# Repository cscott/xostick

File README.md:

This is a simple Open Hardware peripheral for the OLPC XO-1/1.5/1.75/4.

The files are created using Eagle 6.2.0 on Linux and the SparkFun
footprint libraries.

Some details about the design:

1. Supporting using either the ATtiny85 (lowest cost) or the ATtiny861
   (14 I/Os, slightly more expensive).
2. Based on the Sparkfun AVR Stick
    http://www.sparkfun.com/products/9147
   and thus software will be based on
    http://www.obdev.at/vusb/
   Note that the USB port has been moved to PB3/4 so software for the
   SparkFun AVR Stick will not work without modification.
3. The PCB we're working with is 0.8mm (0.031"); a USB plug "is supposed to be
   2.4mm (0.093") but you can get away with 1.6mm (0.062")" (thanks, djgpp)
   Our solution is to put two breakaway tabs on the back of the board.  You
   can break them off and glue them below the USB fingers to make it stay in
   the port better/at all.  One gotcha is that break away PCBs tend to stress
   nearby traces; I've tried to give them adequate clearance.  We're also
   putting copper fills on the PCBs to make them thicker (thanks again, djgpp).
   The PCB we have also has 4 layers, but I've routed this board with only
   the top and bottom so that 2 layer reproductions will work just fine as
   well.  The inner two layers are ground and power planes, which don't
   need to be present to connect the ground and power nets.
4. I'm attempting to bring BOM below $1/student and part count down as low as
   possible as well.  As a result, we're skimping a bit on ferrites and
   bypass caps.
5. There are pads for populating a mini USB B connector, so you can
   put this on a cable (and avoid the glue-the-PCBs-together dance).
6. The XO Stick has a standard arduino shield pinout.  This lets it be
   piggybacked on another XO Stick for programming, or piggy backed on
   an XOrduino to control a turtle robot.  Standard arduino shields will
   probably *not* work, since not all pins are connected -- but they might!
7. To program one XO Stick from an XOrduino, the RST header on the
   target should be put in the "PROG" position so that the programmer
   can drive it via arduino pin 0.  To program an XO Stick from another
   XO Stick, both RST headers should be in the "NORM" position, and
   the programmer needs to have the RSTDISBL fuse programmed, so that it
   can use PB5 ('85) or PB7 ('861) as an output.  Note that once RSTDISBL
   is programmed, the device can't be programmed using the ICSP port
   until RSTDISBL is unprogrammed using the high-voltage programming method.
8. The XO Stick currently needs an external programmer.
   Can we write a USB DFU bootloader using v-usb?
   Something like:

        http://www.obdev.at/products/vusb/usbasploader.html
        http://embedded-creations.com/projects/attiny85-usb-bootloader-overview/
        https://github.com/embedded-creations/USBaspLoader-tiny85

  -- C. Scott Ananian, 2012-06-09; revised 2012-07-30, 2012-08-08

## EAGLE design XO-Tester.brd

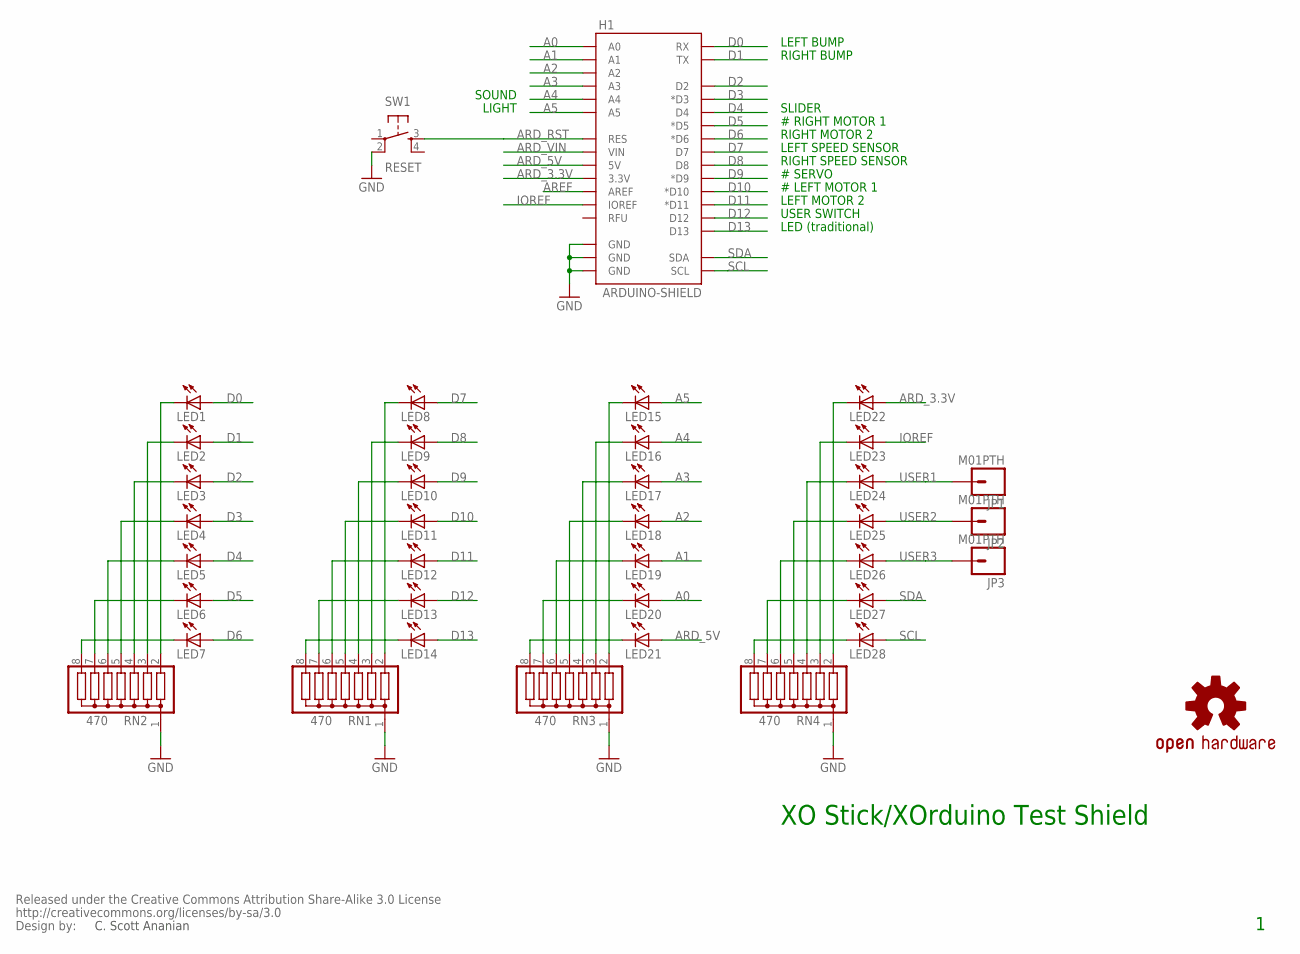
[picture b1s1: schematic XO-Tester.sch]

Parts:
H1: ARDUINO-SHIELD; ARDUINO-SHIELD-VIAS-HOLES
JP1, JP2, JP3: M01PTH; 1X01
LED1, LED2, LED3, LED4, LED5, LED6, LED7, LED8, LED9, LED10, LED11, LED12, LED13, LED14, LED15, LED16, LED17, LED18, LED19, LED20, LED21, LED22, LED23, LED24, LED25, LED26, LED27, LED28: LED3MM-KIT
RN1, RN2, RN3, RN4: 470; SIL8
SW1: RESET; TACTILE-PTH
U$1: OSHW-LOGOM; OSHW-LOGO-M
U$4: CREATIVE_COMMONS

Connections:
A0: H1.A0, LED20.A
A1: H1.A1, LED19.A
A2: H1.A2, LED18.A
A3: H1.A3, LED17.A
A4: H1.A4, LED16.A
A5: H1.A5, LED15.A
ARD_3.3V: H1.3.3V, LED22.A
ARD_5V: H1.5V, LED21.A
ARD_RST: H1.RES, SW1.3
ARD_VIN: H1.VIN
AREF: H1.AREF
D0: H1.RX, LED1.A
D1: H1.TX, LED2.A
D2: H1.D2, LED3.A
D3: H1.D3 (*D3), LED4.A
D4: H1.D4, LED5.A
D5: H1.D5 (*D5), LED6.A
D6: H1.D6 (*D6), LED7.A
D7: H1.D7, LED8.A
D8: H1.D8, LED9.A
D9: H1.D9 (*D9), LED10.A
D10: H1.D10 (*D10), LED11.A
D11: H1.D11 (*D11), LED12.A
D12: H1.D12, LED13.A
D13: H1.D13, LED14.A
GND: H1.GND@0 (GND), H1.GND@1 (GND), H1.GND@2 (GND), RN1.1, RN2.1, RN3.1, RN4.1, SW1.2
IOREF: H1.IOREF, LED23.A
unnamed: LED8.K (C), RN1.2
unnamed: LED9.K (C), RN1.3
unnamed: LED1.K (C), RN2.2
unnamed: LED2.K (C), RN2.3
unnamed: LED3.K (C), RN2.4
unnamed: LED4.K (C), RN2.5
unnamed: LED5.K (C), RN2.6
unnamed: LED6.K (C), RN2.7
unnamed: LED7.K (C), RN2.8
unnamed: LED10.K (C), RN1.4
unnamed: LED11.K (C), RN1.5
unnamed: LED12.K (C), RN1.6
unnamed: LED13.K (C), RN1.7
unnamed: LED14.K (C), RN1.8
unnamed: LED15.K (C), RN3.2
unnamed: LED16.K (C), RN3.3
unnamed: LED17.K (C), RN3.4
unnamed: LED18.K (C), RN3.5
unnamed: LED19.K (C), RN3.6
unnamed: LED20.K (C), RN3.7
unnamed: LED21.K (C), RN3.8
unnamed: LED22.K (C), RN4.2
unnamed: LED23.K (C), RN4.3
unnamed: LED24.K (C), RN4.4
unnamed: LED25.K (C), RN4.5
unnamed: LED26.K (C), RN4.6
unnamed: LED27.K (C), RN4.7
unnamed: LED28.K (C), RN4.8
SCL: H1.SCL, LED28.A
SDA: H1.SDA, LED27.A
USER1: JP1.1, LED24.A
USER2: JP2.1, LED25.A
USER3: JP3.1, LED26.A

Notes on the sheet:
C. Scott Ananian
XO Stick/XOrduino Test Shield
# RIGHT MOTOR 1
# SERVO
# LEFT MOTOR 1
LEFT BUMP
RIGHT BUMP
SLIDER
RIGHT MOTOR 2
LEFT SPEED SENSOR
RIGHT SPEED SENSOR
LEFT MOTOR 2
USER SWITCH
LED (traditional)
SOUND
LIGHT

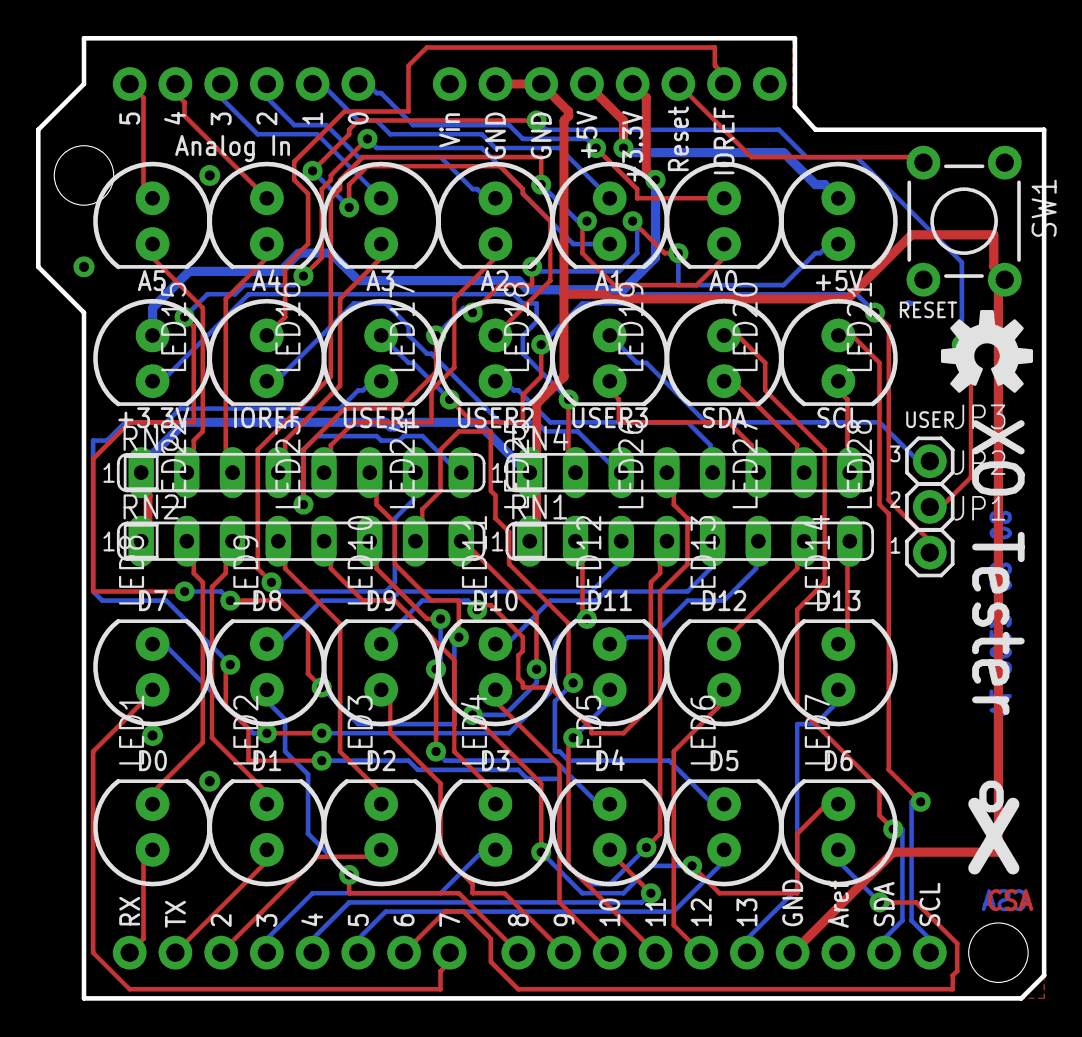
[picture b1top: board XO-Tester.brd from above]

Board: 2 copper layers, 55.9 x 53.3 mm, 39 parts (0 on the bottom side), 58 nets.

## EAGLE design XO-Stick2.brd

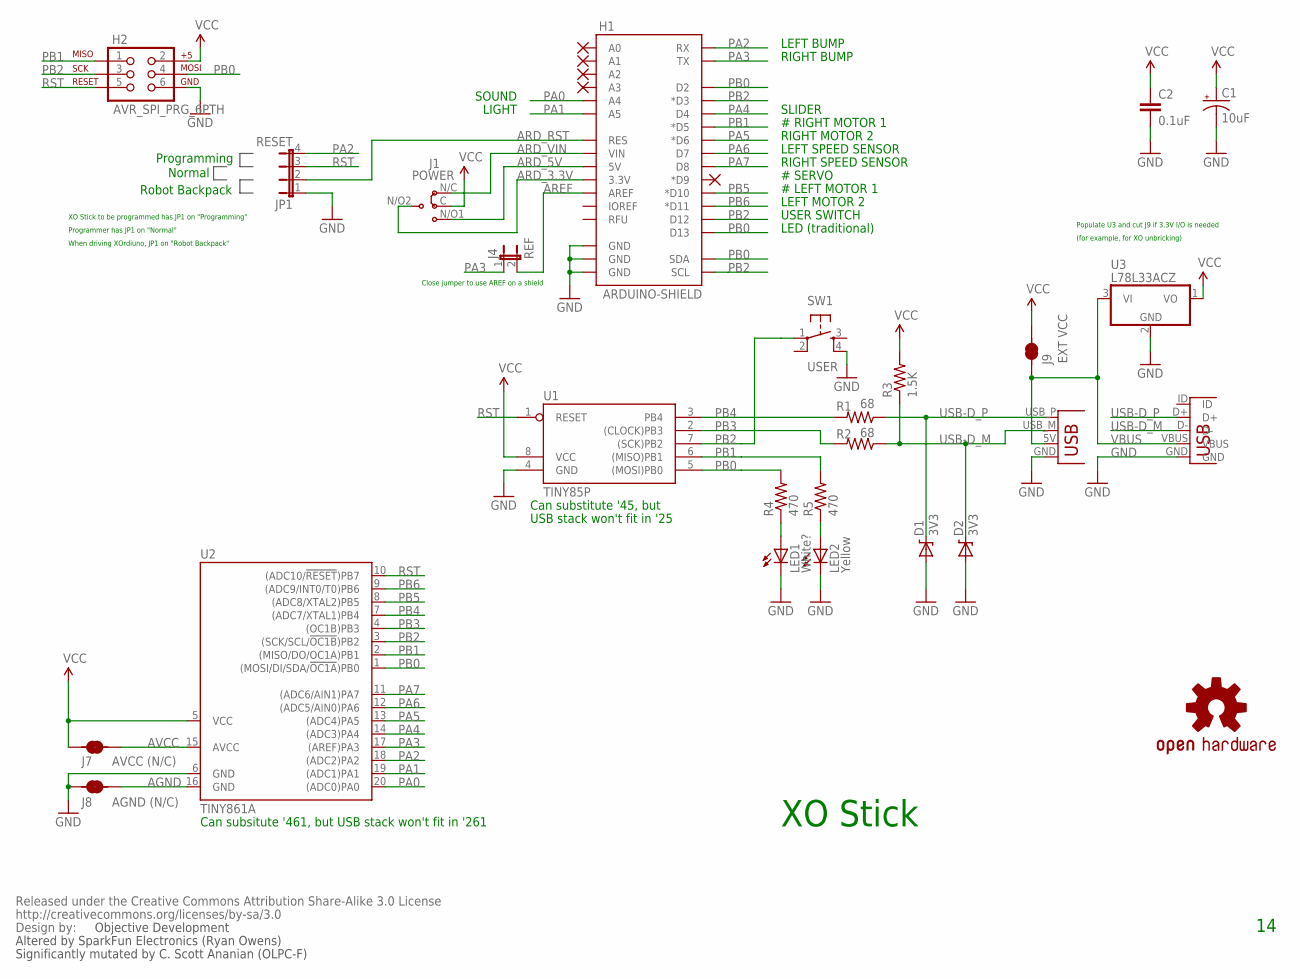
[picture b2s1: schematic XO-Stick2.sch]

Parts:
C1: 10uF; CPOL-RADIAL-10UF-25V
C2: 0.1uF; CAP-PTH-SMALL-KIT
D1, D2: 3V3; DIODE-ZENER
H1: ARDUINO-SHIELD; ARDUINO-SHIELD-VIAS-HOLES
H2: AVR_SPI_PRG_6PTH; 2X3
J1: POWER; JP4-TRACE-NOCONFLICT
J4: REF; SJ-2S-NO
J7: AVCC (N/C); SJ-2S-BOT-TRACE-NOCONFLICT
J8: AGND (N/C); SJ-2S-BOT-TRACE-NOCONFLICT
J9: EXT VCC; SJ-2S-BOT-TRACE-NOCONFLICT-PAD
JP1: RESET; JP4
LED1: White?; LED3MM-KIT
LED2: Yellow; LED3MM-KIT
R1, R2: 68; AXIAL-0.3-KIT
R3: 1.5K; AXIAL-0.3-KIT
R4, R5: 470; AXIAL-0.3-KIT
SW1: USER; TACTILE-PTH
U1: TINY85P; DIL08
U2: TINY861A; DIL20
U3: L78L33ACZ; TO92
U$1: OSHW-LOGOM; OSHW-LOGO-M
U$4: CREATIVE_COMMONS
X1: USBPCB; USB-A-PCB
X2: USBMINIB; USB-MB-H2

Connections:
AGND: J8.2, U2.16 (GND)
ARD_3.3V: H1.3.3V, J1.N/O2
ARD_5V: H1.5V, J1.N/O1
ARD_RST: H1.RES, JP1.2
ARD_VIN: H1.VIN, J1.N/C
AREF: H1.AREF, J4.2
AVCC: J7.2, U2.15 (AVCC)
GND: C1.2 (-), C2.2, D1.P$2 (A), D2.P$2 (A), H1.GND@0 (GND), H1.GND@1 (GND), H1.GND@2 (GND), H2.6, J8.1, JP1.1, LED1.K (C), LED2.K (C), SW1.4, U1.4 (GND), U2.6 (GND), U3.2 (GND), X1.GND, X2.GND
unnamed: LED1.A, R4.P$1 (1)
unnamed: LED2.A, R5.P$1 (1)
PA0: H1.A4, U2.20 ((ADC0)PA0)
PA1: H1.A5, U2.19 ((ADC1)PA1)
PA2: H1.RX, JP1.4, U2.18 ((ADC2)PA2)
PA3: H1.TX, J4.1, U2.17 ((AREF)PA3)
PA4: H1.D4, U2.14 ((ADC3)PA4)
PA5: H1.D6 (*D6), U2.13 ((ADC4)PA5)
PA6: H1.D7, U2.12 ((ADC5/AIN0)PA6)
PA7: H1.D8, U2.11 ((ADC6/AIN1)PA7)
PB0: H1.D2, H1.D13, H1.SDA, H2.4, R4.P$2 (2), U1.5 ((MOSI)PB0), U2.1 ((MOSI/DI/SDA/!OC1A!)PB0)
PB1: H1.D5 (*D5), H2.1, R5.P$2 (2), U1.6 ((MISO)PB1), U2.2 ((MISO/DO/OC1A)PB1)
PB2: H1.D3 (*D3), H1.D12, H1.SCL, H2.3, SW1.1, U1.7 ((SCK)PB2), U2.3 ((SCK/SCL/!OC1B!)PB2)
PB3: R2.P$2 (2), U1.2 ((CLOCK)PB3), U2.4 ((OC1B)PB3)
PB4: R1.P$2 (2), U1.3 (PB4), U2.7 ((ADC7/XTAL1)PB4)
PB5: H1.D10 (*D10), U2.8 ((ADC8/XTAL2)PB5)
PB6: H1.D11 (*D11), U2.9 ((ADC9/INT0/T0)PB6)
RST: H2.5, JP1.3, U1.1 (RESET), U2.10 ((ADC10/!RESET!)PB7)
USB-D_M: D2.P$1 (C), R2.P$1 (1), R3.P$1 (1), X1.USB_M (D-), X2.D-
USB-D_P: D1.P$1 (C), R1.P$1 (1), X1.USB_P (D+), X2.D+
VBUS: J9.1, U3.3 (VI), X1.5V (VBUS), X2.VBUS
VCC: C1.1 (+), C2.1, H2.2, J1.C, J7.1, J9.2, R3.P$2 (2), U1.8 (VCC), U2.5 (VCC), U3.1 (VO)

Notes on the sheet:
Objective Development
Altered by SparkFun Electronics (Ryan Owens)
XO Stick
# RIGHT MOTOR 1
# SERVO
# LEFT MOTOR 1
LEFT BUMP
RIGHT BUMP
SLIDER
RIGHT MOTOR 2
LEFT SPEED SENSOR
RIGHT SPEED SENSOR
LEFT MOTOR 2
USER SWITCH
LED (traditional)
SOUND
LIGHT
Significantly mutated by C. Scott Ananian (OLPC-F)
Programming
Robot Backpack
Normal
XO Stick to be programmed has JP1 on "Programming"
Programmer has JP1 on "Normal"
When driving XOrdiuno, JP1 on "Robot Backpack"
Close jumper to use AREF on a shield
Can subsitute '461, but USB stack won't fit in '261
Can substitute '45, but
USB stack won't fit in '25
Populate U3 and cut J9 if 3.3V I/O is needed
(for example, for XO unbricking)

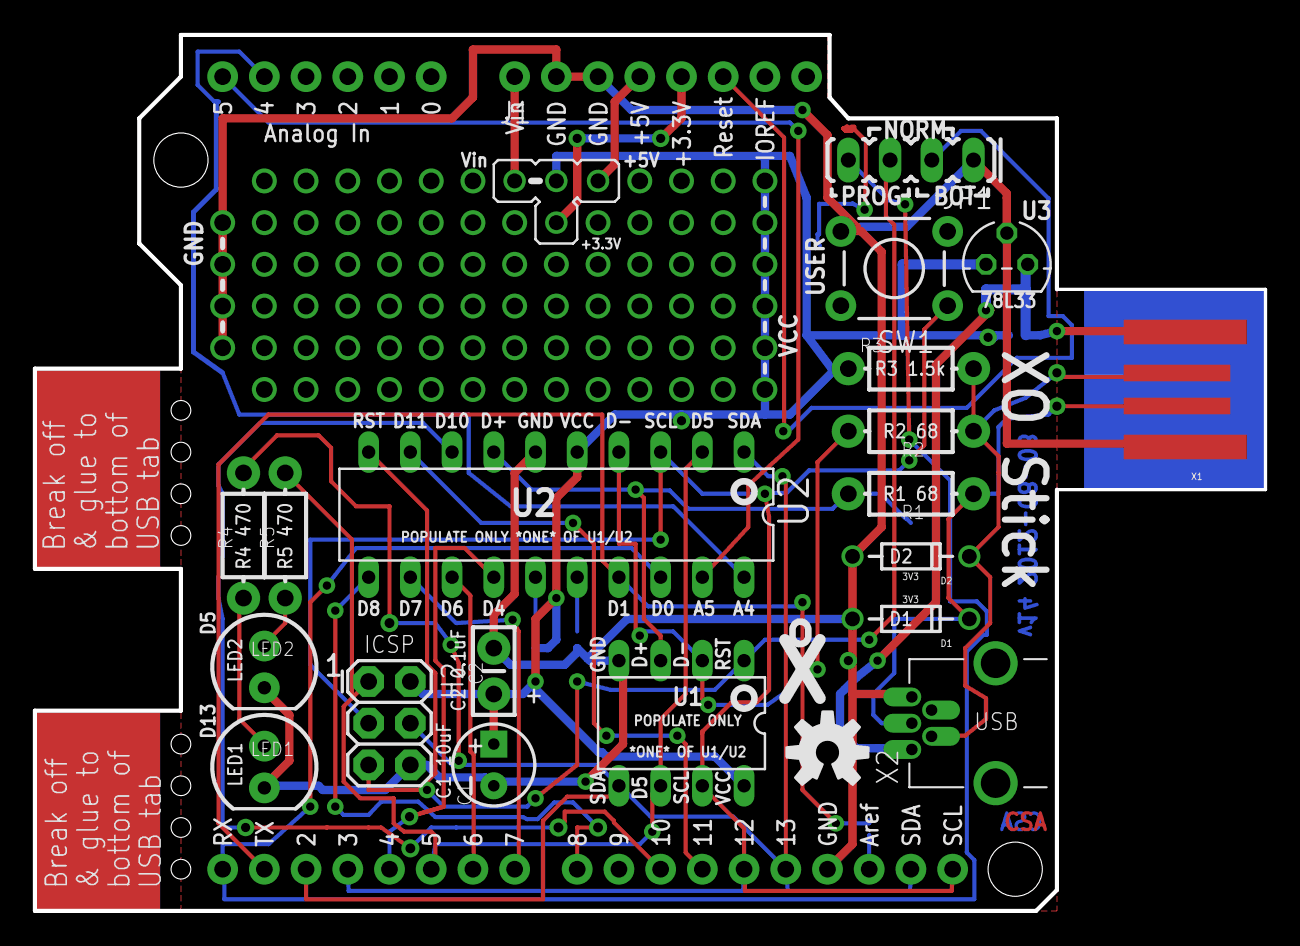
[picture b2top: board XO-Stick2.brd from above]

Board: 2 copper layers, 74.9 x 53.3 mm, 27 parts (1 on the bottom side), 30 nets.

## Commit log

2012-06-05 SparkFun version of AVR Stick.
2012-06-05 ATtiny261/ATtiny85 version, w/ new headers, not routed.
2012-06-05 Routed v1 of the XO stick layout.
2012-06-06 2012-06-07 version of XO stick: add USB mini-B, switch, zeners.
2012-06-06 v3: tweak dimensions for better fit on XO, switch to 3mm LED, add silkscreen.
2012-06-06 Add README for github.
2012-06-06 v4: thicker power/gnd traces, add fill to backside of USB conn for thickness.
2012-06-06 v5: add ground and VCC planes.
2012-06-09 Rename files from AVR-Stick to XO-Stick.
2012-06-09 Write more details information about the design constraints, choices made, etc.
2012-06-09 README: Remove a wayward comma; nearly->nearby (thanks, cjb).
2012-06-10 Update BOM w/ digikey part #s.
2012-06-20 Add gerbers for 4 layer PCB, just in case that's useful.
2012-07-18 Check-in assembly notes from A1 build of XO Stick.
2012-07-28 v6 of schematic: add xorduino compatible shields, prototype area.
    Too many selectable headers in this version, need to trim some for space.
    Also, we need to move the USB connector in order to nest tightly with
    XOrduino board.
2012-07-30 v7 of board/schematic. Fixed remaining issues with v6. 2-layer routing.
2012-07-30 Remove old v5 gerbers to avoid confusion.
2012-07-30 Update README to match XO Stick v7.
2012-07-31 XO Stick v8: add jumper between VBUS and VCC; make SDA/SCL jumpers N/C.
    SDA and SCL jumpers need to be closed in order to program XO Stick from
    an XOrduino. Splitting VBUS from VCC is needed in order to make a 3.3v
    variant XO Stick for XO unbricking.
2012-07-31 XO Stick v9: add silkscreen to break-off tabs, move some traces.
    Moved traces away from break-off tabs and removed one trace from the
    top side of the USB connector.
2012-07-31 XO Stick v10: moved USB connector up 10 mil to better fit vertical XO port.
2012-07-31 Tweak USB mini-B connector footprint; restring to 8mil min.
    USB connector footprint was restricting the min pad width in our restring.
    Noticed that USB footprint was really loose, too. Checked against datasheet,
    tightened up holes and switched to oblong pads. Restring to 8mil min,
    which required a few minor trace adjustments.
2012-08-01 Add optional 3.3v TO-92 LDO regulator, for use when unbricking XOs.
2012-08-03 XO Stick v13: silkscreen additions; rename nets in schematic for less confusion.
2012-08-08 Minor tweak to schematic: swap SCL/SDA signals to match their order on the PCB.
2012-08-08 XO Stick v14: move USB to PB3/4 (Louis Beaudoin suggestion).
    This allows more straightforward use of the XO Stick as a programmer,
    and of the XO Stick's I2C bus.
    It complicates use of the '85 to drive the XOrduino bot, but that's probably
    a reasonable sacrifice.
2012-08-08 Update README to match XO Stick v14.
2012-08-08 Add a simple Arduino shield to aid in testing XO Stick and XOrduino.
2012-08-10 Add drill table layer; regenerate Gerbers in vendor-approved format.
    The drill table was made with drillegend-stack.ulp. It has a problem deleting
    an existing drill table (see
    http://www.eaglecentral.ca/forums/index.php/mv/msg/46577/145423/
    ) so I've saved the .brd file with the drill legend as XO-Stick2-drilltable.brd.
    If changes are necessary to XO-Stick2.brd, regenerate XO-Stick2-drilltable.brd
    from XO-Stick2.brd after making the changes.
2012-08-10 Gerbers for the test shield.
2013-03-01 Update BOM and assembly notes for XO Stick v14.
2013-03-01 Add cut-and-pasteable BOM for easier ordering from DigiKey.
2015-04-22 Commit notes on v14 which were lying around on disk.

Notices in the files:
parts and their libraries:
SparkFun: Released under the Creative Commons Attribution Share-Alike 3.0 License
SparkFun: http://creativecommons.org/licenses/by-sa/3.0
SparkFun-Passives: Licensing: CC v3.0 Share-Alike You are welcome to use this library for commercial purposes.
